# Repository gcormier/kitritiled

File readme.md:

# kitritiled
This is a copy of Ted Yapo's tritiled project from https://github.com/tedyapo/tritiled. It is based on the V3.1 design.
I did my best to reproduce the schematic, and optimize it for automated assembly as opposed to hand-assembly. As a result, it uses some slightly different parts, such as 0402 components when possible.

## Firmware
kitritiled.hex is the firmware to flash. I lost track of the changes I made to the original firmware by Ted - if you use his v30 runtime selectable, it almost works, except the button doesn't seem to trigger the interrupt. It's been a few years since I looked at it, so I pulled the firmware off one of my v1 devices and
that's all I have unfortunately. `modes.h` is also changed slightly from his.

## Flashing
I use MPLAB IPE to flash the firmware with a MPLAB PICkit 5.

## Usage
The device has 10 power levels, and starts on the brightest setting.

When you first insert the battery, you have a 10 second window during which you can configure the power level.

This is done by pushing the button on the device. Once you hit the lowest power level, it will start back at the highest.

When you are done, leave it alone. It will blink the LED to indicate the power level. eg 1 blink for level 1, 2 blinks for level 2, etc.

It will do this three times, at which point it will then lock in at that power level and the button will no longer work.

If you want to change the power level, you need to remove the battery, and wait for the light to go out completely before repeating the above process.

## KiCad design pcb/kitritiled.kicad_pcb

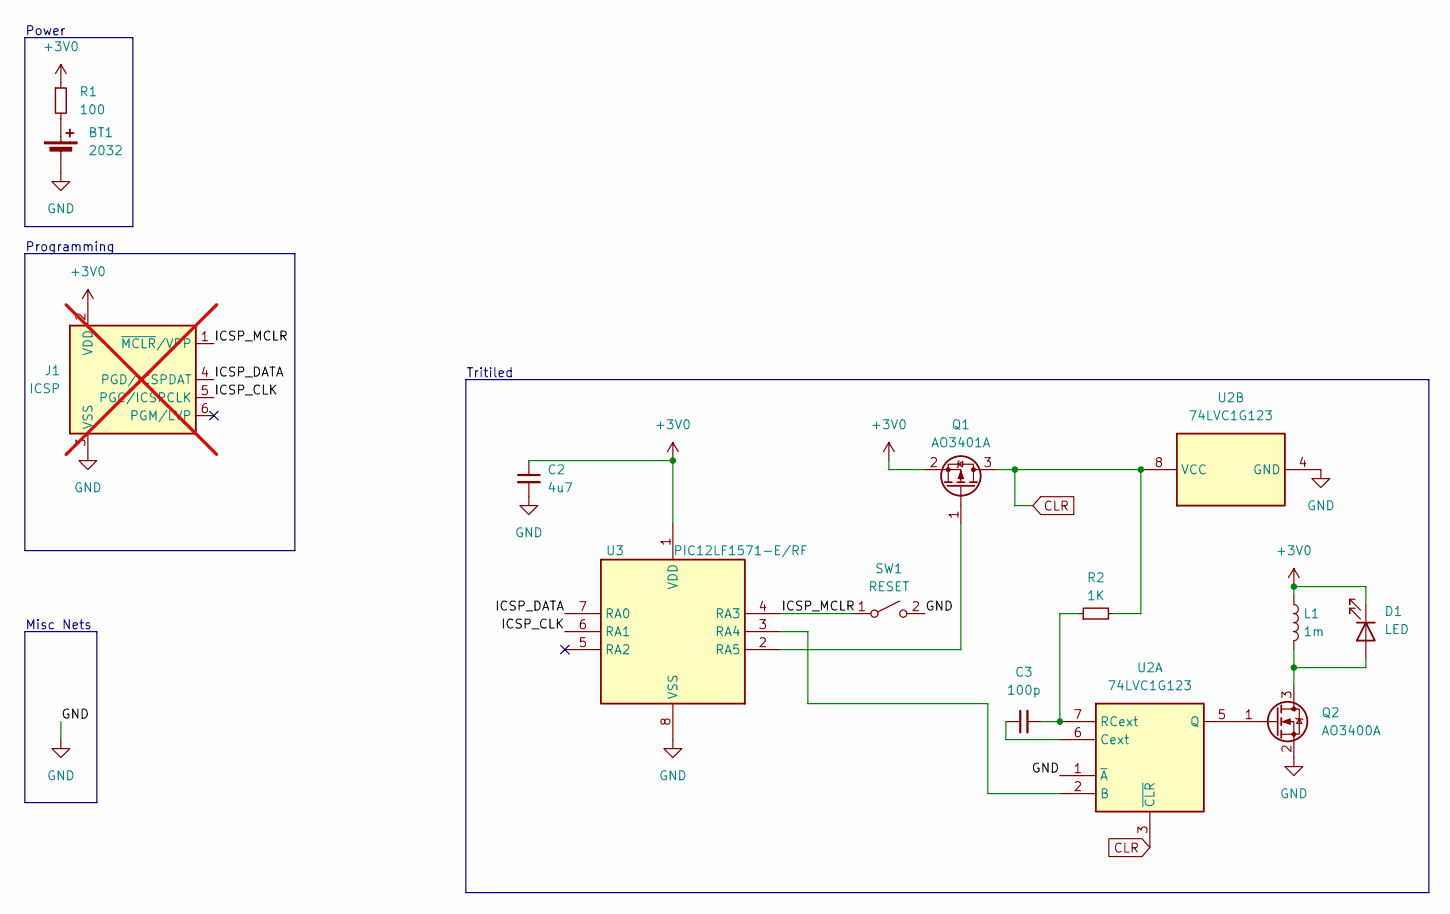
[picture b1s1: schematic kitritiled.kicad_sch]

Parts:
BT1: 2032; BAT_BAT-HLD-001-THM
C2: 4u7; C_0402_1005Metric; LCSC C23733
C3: 100p; C_0402_1005Metric; LCSC C1546
D1: LED; LED_Cree-XP; DIGIKEY XPEBGR-L1-0000-00F02
J1: ICSP; PinHeader_1x05_P1.27mm_Vertical; not fitted
L1: 1m; L_Sunlord_SWPA6028S; LCSC C133757
Q1: AO3401A; SOT-23; LCSC C15127
Q2: AO3400A; SOT-23; LCSC C20917
R1: 100; R_0402_1005Metric; LCSC C25076
R2: 1K; R_0402_1005Metric; LCSC C11702
SW1: RESET; SW_Push_1P1T_XKB_TS-1187A; LCSC C318884
U2: 74LVC1G123; TSSOP-8_3x3mm_P0.65mm; LCSC C513291
U3: PIC12LF1571-E/RF; DFN-8-1EP_3x3mm_P0.65mm_EP1.55x2.4mm; LCSC C635312

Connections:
+3V0: C2.1, D1.1 (K), J1.2 (VDD), L1.1, Q1.2 (S), R1.1, U3.1 (VDD)
/ICSP_CLK: J1.5 (PGC/ICSPCLK), U3.6 (RA1)
/ICSP_DATA: J1.4 (PGD/ICSPDAT), U3.7 (RA0)
/ICSP_MCLR: J1.1 (~MCLR/VPP), SW1.1 (A), U3.4 (RA3)
CLR: Q1.3 (D), R2.2, U2.3 (~CLR), U2.8 (VCC)
GND: BT1.2 (-), C2.2, J1.3 (VSS), Q2.2 (S), SW1.2 (B), U2.1 (~A), U2.4 (GND), U3.8 (VSS)
unnamed: BT1.1 (+), R1.2
unnamed: D1.2 (A), L1.2, Q2.3 (D)
unnamed: Q1.1 (G), U3.2 (RA5)
unnamed: Q2.1 (G), U2.5 (Q)
unnamed: U2.2 (B), U3.3 (RA4)
unnamed: C3.1, U2.6 (Cext)
unnamed: C3.2, R2.1, U2.7 (RCext)

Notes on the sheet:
Tritiled
Programming
Misc Nets
Power

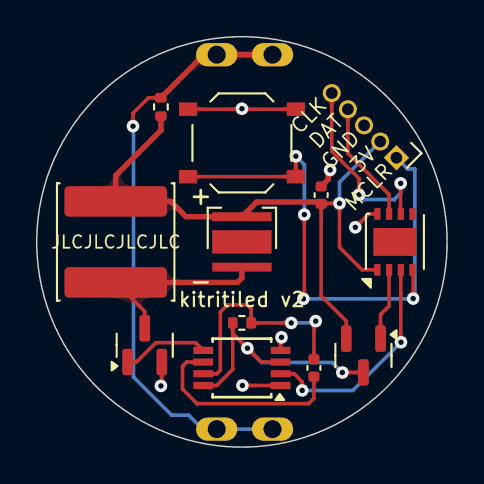
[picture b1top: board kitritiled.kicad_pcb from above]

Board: 2 copper layers, 22.8 x 22.8 mm, 13 parts (1 on the bottom side), 13 nets.

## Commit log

2023-10-07 initial
2023-10-07 panel
2023-10-09 license and silkscreen
2023-10-09 nudge
2023-10-09 blender
2023-10-09 new 3d model
2023-10-11 prefab
2023-10-30 jlc pn
2023-10-30 wider spacing
2023-10-30 fix spacing
2023-10-30 again
2023-10-30 spacing
2023-10-30 repanel on change
2023-10-30 panel on tag
2023-10-30 3x3 panel
2023-10-30 fix part number
2023-11-09 holder change
2023-11-12 panel filter
2023-11-12 filter2
2023-11-12 filter on kibot
2023-11-12 remove filter
2023-11-16 exclude kikit from pos
2023-12-28 attiny version
2025-04-03 temp
2025-04-05 pic updates
2025-04-05 new builds
2025-04-05 version
2025-04-05 use dev
2025-04-05 back to main v9
2025-04-05 update panel
2025-04-05 tighter spacing
2025-04-05 render
2025-05-14 Modified firmware for kitritiled
2025-05-14 notes
2025-05-14 usage
2025-05-14 moar
